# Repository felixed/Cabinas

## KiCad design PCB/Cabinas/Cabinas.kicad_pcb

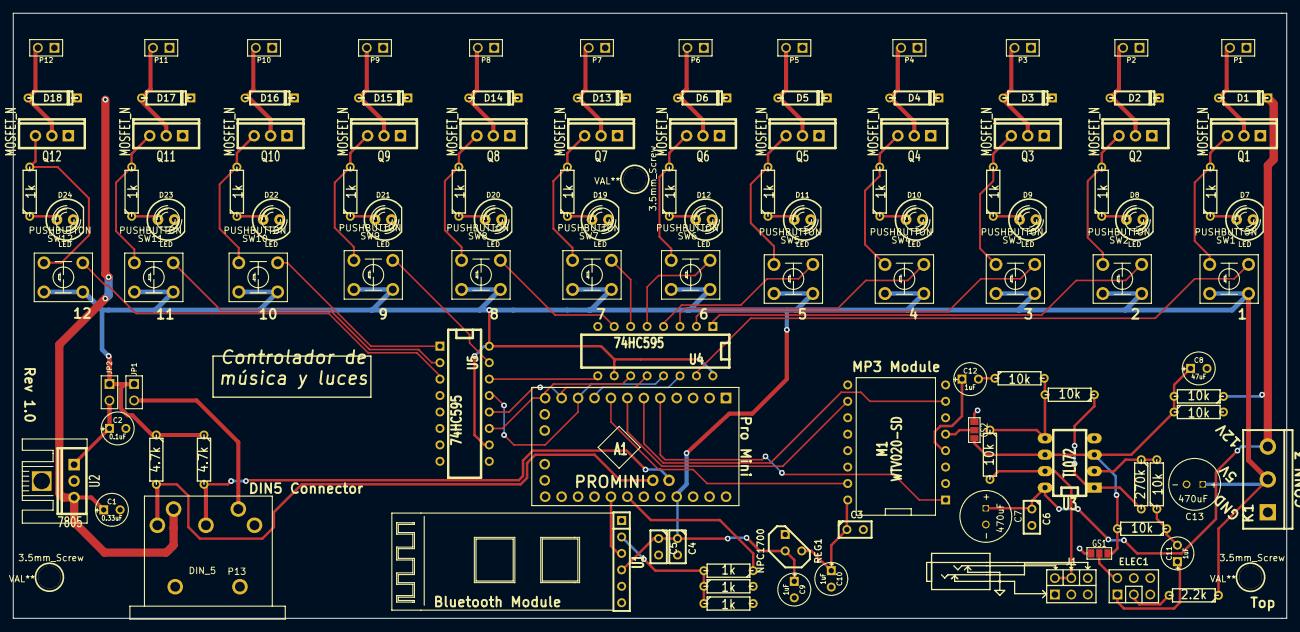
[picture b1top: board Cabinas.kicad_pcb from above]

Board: 2 copper layers, 196.7 x 93.5 mm, 118 parts (0 on the bottom side), 80 nets.

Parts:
3.5mm_Screw, 3.5mm_Screw#2, 3.5mm_Screw#3: VAL**; 3.5mm_Screw
A1: PROMINI; ProMini
C1: 0.33uF; C1V5
C2: 0.1uF; C1V5
C3, C4, C5, C6: 0.1uF; C1
C7, C13: 470uF; CAP_8_3.5
C8: 47uF; C1V5
C9, C10, C11, C12: 1uF; C1V5
D1, D2, D3, D4, D5, D6, D13, D14, D15, D16, D17, D18: DIODE; D3
D7, D8, D9, D10, D11, D12, D19, D20, D21, D22, D23, D24: LED; LED-5MM
ELEC1: ELECTRET_MIC_SUP; pin_array_3x2
GS1, GS2: GS3
J1: JACK_ST_3SW; pin_array_3x2
JP1, JP2: JUMPER; PIN_ARRAY_2X1
K1: CONN_3; bornier3
M1: WTV020-SD; MP3
P1, P2, P3, P4, P5, P6, P7, P8, P9, P10, P11, P12: CONN_2; PIN_ARRAY_2X1
P13: DIN_5; MIDI
Q1, Q2, Q3, Q4, Q5, Q6, Q7, Q8, Q9, Q10, Q11, Q12: MOSFET_N; TO220_MOSFET
R1, R2, R3, R4, R5, R6, R7, R8, R9, R10, R11, R12, R15, R16, R17: 1k; R3
R13, R14: 4.7k; R3
R18, R19, R21, R22, R23, R24, R26: 10k; R3
R20: 270k; R3
R25: 2.2k; R3
REG1: NPC1700; TO92
SW1, SW2, SW3, SW4, SW5, SW6, SW7, SW8, SW9, SW10, SW11, SW12: PUSHBUTTON; TactileSW_2
U1: BTM; btm
U2: 7805; TO220_VERT
U3: TL072; DIP-8__300_ELL
U4, U5: 74HC595; DIP-16__300

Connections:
1: SW1.2, U4.15
2: SW2.2, U4.1
3: SW3.2, U4.2
4: SW4.2, U4.3
5: SW5.2, U4.4
6: SW6.2, U4.5
7: SW7.2, U4.6
8: SW8.2, U4.7
9: SW9.2, U5.15
10: SW10.2, U5.1
11: SW11.2, U5.2
12: SW12.2, U5.3
+3.3V: C3.1, C10.1, M1.16, REG1.3
+5V: A1.25, C4.1, C5.1, C9.1, C13.1, JP1.1, JP2.1, K1.2, R13.1, R14.1, R25.1, REG1.2, SW1.3, SW1.4, SW2.3, SW2.4, SW3.3, SW3.4, SW4.3, SW4.4, SW5.3, SW5.4, SW6.3, SW6.4, SW7.3, SW7.4, SW8.3, SW8.4, SW9.3, SW9.4, SW10.3, SW10.4, SW11.3, SW11.4, SW12.3, SW12.4, U1.4, U4.10, U4.16, U5.10, U5.16
+12V: C1.1, C6.1, C7.1, D1.2, D2.2, D3.2, D4.2, D5.2, D6.2, D13.2, D14.2, D15.2, D16.2, D17.2, D18.2, K1.3, P1.1, P2.1, P3.1, P4.1, P5.1, P6.1, P7.1, P8.1, P9.1, P10.1, P11.1, P12.1, P13.5, R18.1, U2.Vi, U3.8
A0 (RX): A1.21, U1.3
A1 (TX): A1.22, R16.1
GND: A1.4, A1.27, C1.2, C2.2, C3.2, C4.2, C5.2, C6.2, C7.2, C8.2, C9.2, C10.2, C13.2, D7.2, D8.2, D9.2, D10.2, D11.2, D12.2, D19.2, D20.2, D21.2, D22.2, D23.2, D24.2, GS1.1, GS2.1, J1.1, J1.3, J1.5, J1.6, K1.1, M1.8, P13.3, Q1.S, Q2.S, Q3.S, Q4.S, Q5.S, Q6.S, Q7.S, Q8.S, Q9.S, Q10.S, Q11.S, Q12.S, R15.2, R17.2, R19.2, REG1.1, U1.6, U2.GND, U3.4, U4.8, U5.8
I2CSCL: A1.30, P13.1, R14.2
I2CSDA: A1.29, P13.2, R13.2
MP3_BUSY: A1.8, M1.15
MP3_CK: A1.6, M1.7
MP3_DATA: A1.7, M1.10
MP3_OUTPUT: C12.1, M1.4
MP3_RESET: A1.5, M1.1
unnamed: D13.1, P7.2, Q7.D
unnamed: D12.1, R6.1
unnamed: Q6.G, R6.2, SW6.1
unnamed: D19.1, R7.1
unnamed: Q7.G, R7.2, SW7.1
unnamed: D11.1, R5.1
unnamed: Q5.G, R5.2, SW5.1
unnamed: D5.1, P5.2, Q5.D
unnamed: D14.1, P8.2, Q8.D
unnamed: D6.1, P6.2, Q6.D
unnamed: D16.1, P10.2, Q10.D
unnamed: D21.1, R9.1
unnamed: D17.1, P11.2, Q11.D
unnamed: D22.1, R10.1
unnamed: Q10.G, R10.2, SW10.1
unnamed: D20.1, R8.1
unnamed: Q8.G, R8.2, SW8.1
unnamed: Q9.G, R9.2, SW9.1
unnamed: D15.1, P9.2, Q9.D
unnamed: D1.1, P1.2, Q1.D
unnamed: D7.1, R1.1
unnamed: Q1.G, R1.2, SW1.1
unnamed: D4.1, P4.2, Q4.D
unnamed: D9.1, R3.1
unnamed: Q3.G, R3.2, SW3.1
unnamed: D10.1, R4.1
unnamed: Q4.G, R4.2, SW4.1
unnamed: D8.1, R2.1
unnamed: Q2.G, R2.2, SW2.1
unnamed: D2.1, P2.2, Q2.D
unnamed: D3.1, P3.2, Q3.D
unnamed: J1.2, J1.4, R21.2, U3.7
unnamed: ELEC1.3, R25.2
unnamed: C12.2, R24.1
unnamed: C11.2, R22.1, R26.1
unnamed: ELEC1.2, GS1.2
unnamed: GS2.2, M1.5
unnamed: C11.1, ELEC1.1
unnamed: U4.9, U5.14
unnamed: JP1.2, P13.4
unnamed: R15.1, R16.2, R17.1, U1.2
unnamed: D24.1, R12.1
unnamed: Q11.G, R11.2, SW11.1
unnamed: D23.1, R11.1
unnamed: Q12.G, R12.2, SW12.1
unnamed: D18.1, P12.2, Q12.D
unnamed: C2.1, JP2.2, U2.Vo
unnamed: R20.1, R22.2, U3.2
unnamed: R21.1, R23.2, R24.2, U3.5
unnamed: R20.2, R23.1, U3.1
SR_CLK: A1.12, U4.11, U5.11
SR_Input: A1.9, U4.14
SR_LCLK: A1.11, U4.12, U5.12
SR_OE: A1.10, U4.13, U5.13
Vbias: C8.1, GS1.3, GS2.3, R18.2, R19.1, R26.2, U3.3, U3.6

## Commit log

2014-07-08 Cabinas
    Cabinas
2014-07-08 Added stuff
    Added stuff
2014-07-09 Cambios
    Cambio en los capacitores de desacoplamiento y sus footprints.
2014-07-10 Cambios
    Cambio de pines para el módulo MP3
2014-07-10 codigo de prueba
    codigo de prueba
2014-07-13 Shift registers
    Se añadieron shift registers
2014-07-14 Revision final
    Revision final
2014-07-15 Actualizacion del codigo
    Actualizacion del codigo
2014-07-16 Actualizacion de codigo
    Actualizacion de codigo
2014-07-16 Botonera PCB
    Botonera PCB
2014-07-16 Botonera
    Botonera
2014-07-18 Botonera Panel
    Botonera Panel
2014-07-30 ?
    ?
2014-07-30 stackdump
    stackdump
2014-08-04 Create cableado
